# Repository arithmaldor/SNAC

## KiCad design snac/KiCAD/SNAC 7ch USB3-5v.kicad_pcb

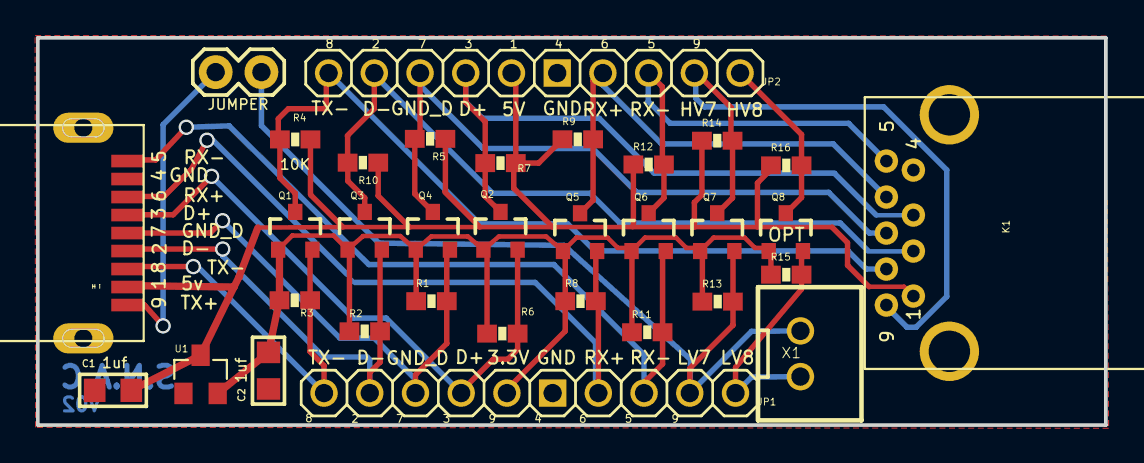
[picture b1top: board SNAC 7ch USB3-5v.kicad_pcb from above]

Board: 2 copper layers, 59.3 x 21.5 mm, 33 parts (0 on the bottom side), 19 nets.

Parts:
C1, C2: 1uf; C0805
JP1, JP2: PINHD-1X10_2.54-S; 1X10-S
JP3: JUMPER-2PTH; 1X02
K1: 692121030100
K2: 692112030100
Q1, Q2, Q3, Q4, Q5, Q6, Q7, Q8: BSS138; SOT23-3
R1, R2, R3, R4, R5, R6, R7, R8, R9, R10, R11, R12, R13, R14, R15, R16: 10K; 0603-RES
U1: PMIC-LDO-XC6206P332MR-G(SOT23); SOT-23
X1: JST-XH-02-PIN-ROUND-PAD; JST-XH-02-PACKAGE-ROUND-PAD

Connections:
/GND: C1.1, C2.1, JP1.6, JP2.6, K1.4, K2.4, U1.1
/HV1: JP2.1, K1.8, Q1.3, R4.2
/HV2: JP2.2, K1.2, Q3.3, R10.2
/HV3: JP2.3, K1.7, Q4.3, R5.2
/HV4: JP2.4, K1.3, Q2.3, R7.2
/HV5: JP2.7, K1.6, Q5.3, R9.2
/HV6: JP2.8, K1.5, Q6.3, R12.2
/HV7: JP2.9, K1.9, Q7.3, R14.2
/HV8: JP2.10, Q8.3, R16.2
/J1: JP3.1, K2.9
/LV1: JP1.1, K2.8, Q1.2, R3.2
/LV2: JP1.2, K2.2, Q3.2, R2.2
/LV3: JP1.3, K2.7, Q4.2, R1.2
/LV4: JP1.4, K2.3, Q2.2, R6.2
/LV5: JP1.7, K2.6, Q5.2, R8.2
/LV6: JP1.8, K2.5, Q6.2, R11.2
/LV7: JP1.9, JP3.2, Q7.2, R13.2, X1.1
/LV8: JP1.10, Q8.2, R15.2, X1.2
VCC: C1.2, C2.2, JP1.5, JP2.5, K1.1, K2.1, Q1.1, Q2.1, Q3.1, Q4.1, Q5.1, Q6.1, Q7.1, Q8.1, R1.1, R2.1, R3.1, R4.1, R5.1, R6.1, R7.1, R8.1, R9.1, R10.1, R11.1, R12.1, R13.1, R14.1, R15.1, R16.1, U1.2, U1.3

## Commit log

2020-06-27 KiCAD and PCBA
    Added KiCAD version, created position and BOM files for JLCPCB assembly service
